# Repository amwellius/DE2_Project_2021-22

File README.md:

**2021**, Faculty of Electrical Engineering and Communication [FEKT](https://www.fekt.vut.cz/) <br/> 
 <br/>
# WATER TANK CONTROLLER

### Team members

- **Gregor Karetka**   &nbsp;                             *id=221053*   &nbsp;&nbsp;    <br/> 
- **Martin Knob**   &nbsp;&nbsp;&nbsp;&nbsp;&nbsp;               *id=221054*   &nbsp;&nbsp;     <br/>
- **Filip Kocum**   &nbsp;&nbsp;&nbsp;&nbsp;&nbsp;&nbsp;   *id=221055*   &nbsp;&nbsp;     <br/> 
- **Samuel Košík**   &nbsp;&nbsp;&nbsp;&nbsp;              *id=221056*   &nbsp;&nbsp;    <br/> 

Link to this file in GitHub repository:

[https://github.com/amwellius/DE2_Project_2021-22](https://github.com/amwellius/DE2_Project_2021-22)

### Table of contents

* [Project objectives](#objectives)
* [Hardware description](#hardware)
* [Libraries description](#libs)
* [Main application](#main)
* [Video and Documentation](#video)
* [References](#references)

## Project objectives

This simple but useful application will help you to fully control your **water tank** (not only!) in the garden. Do you want to know how much water is left? Do you want to refill the tank? Or are you interested in controlling your own independent application based on the volume left in the tank? <br/>
No problem! <br/>
With our **Water Tank Controller** you will be able to:
- know **current water level** in centimeters, percentage and liters,
- see **maximum** volume of the tank,
- use relays to control pump,
- prevent **owerflowing** the tank with extra sensor,
- see **graphic representation** of the water level.

## Hardware description

As main programming board **Arduino UNO** is used. For displaying results **Nokia 5110 LCD display** was selected, **Relay module** and **button** (optional). Ultrasonic **HC-SR04** is the primary water level sensor. There is **Capacitive Soil Moisture Sensor v1.2** used as backup to prevent overflowing the tank when debris (leaves, flowers, pollen, ...) clogs in the tank sink. By small adjustments in the code it can be transformed into rain detector. 

### Arduino UNO + breadboard 
[Datasheet](https://github.com/amwellius/DE2_Project_2021-22/blob/main/Datasheets%20%2B%20DOCs/ATMega_328P_datasheet.pdf)

&nbsp;

&nbsp;

Application uses a number of digital I/O pins, analog input pins and 3.3 V and 5 V power supply. Schematic can be seen here [SCHEMATIC](https://github.com/amwellius/DE2_Project_2021-22/blob/main/schematic.pdf). 

### Nokia 5110 LCD display 
[Datasheet](https://github.com/amwellius/DE2_Project_2021-22/blob/main/Datasheets%20%2B%20DOCs/Nokia5110_datasheet.pdf)

&nbsp;

&nbsp;

All output data is shown on Nokia LCD display. Third party library has been edited in order to use it with *Arduino UNO* and image display function was implemented. Display's resolution **84x48**  allows to display many useful data or **graphic representation** of water level as well. Drawn images were converted to **byte arrays** to simplify the usege in *Microchip Studio*. <br/>
Picture below shows possible states. <br/>

<br/>
Also some resistors had to be used to properly connect LCD to Arduino board.

### Relay Module 
[Datasheet](https://components101.com/switches/5v-single-channel-relay-module-pinout-features-applications-working-datasheet)

&nbsp;

&nbsp;

Usage of relay(s) is optional. **C code** has implemented section which toggles the relay module by pressing **button** connected to Arduio UNO. It can be connected to pump or solenoid to enable watering plants or other uses of the water. **A capacitor** inserted in cicruit (as RL low pass filter) helps to stabilize *overoscillations* generated by the button. By using hardware filter we were able to implement button handling with interrupt.

### UltraSonic sensor HC-SR04
[Datasheet](https://github.com/amwellius/DE2_Project_2021-22/blob/main/Datasheets%20%2B%20DOCs/HCSR04.pdf)

&nbsp;

&nbsp;

Main sensor for measuring the water level of the tank is **HC-SR04**. After entering its **dimensions** the sensor is calibrated. Providing it with short 10us pulse will result in receiving 8 cycles of 40KHz signal. This will be given by *ECHO pin*, so received value will be the time the wave travelled to the water and back to the sensor. Final distance can be obtained by this equation: 

&nbsp;

&nbsp;

Where **t** is the received value on *ECHO pin* and **0.034** cames from the speed of sound *(340 m/s = 0.034 m/us)*. Sound wave travels from sensor to water, but from water to the sensor as well. That is why the result has to be devided by two. *Arduino UNO's* **timers** are used to measure width of received square signal. After calculation, distance in milimeters is returned. Its value is sent to other functions, so supplementary data can be sent to display on *Nokia LCD*.

### Capacitive Water Lever Sensor

[Datasheet](https://github.com/amwellius/DE2_Project_2021-22/blob/main/Datasheets%20%2B%20DOCs/water_level_sensor.pdf)

It is situated **a few centimeters** above main ultrasonic sensor. If ultrasonic **fails**, this option will prevent **overflowing** the water tank. Display will print **System overflow** message. Relay module can the programmed for specific behavior after getting to *overflow* stage, too (optional). <br/>
Sensor is connected to *analog input* pin, *GND* and *Vcc=5 V*. Its usage describes table below. <br/>
   
   | **Value** | **Results in** |
   | :-: | :-: |
   | <=850 | System working properly. |
   | >850 | System malfunction! |

&nbsp;

## Libraries description

Code for this application was written in **C**, compilated using **AVR/GNU C compiler** and **MicroChip Studio**. Project consists of several libraries, list of all files can be found below:
   - `main.h`- main function header,
   - `main.c` - includes main procedures and functions,
   - `english_font.h` - characters for LCD display,
   - `nokia_5110_lcd.h` - header for LCD display,
   - `nokia_5110_lcd.c` - functions for LCD controlling,
   - `water_symbols.h` - header for c file,
   - `water_symbols.c` - byte maps (figures on LCD), 
   - `gpio.h` - input/output header,
   - `gpio.c` - input/output functions,
   - `timer.h` - header for timers in *Arduino UNO*,
   - `HC-SR04.h` - header for *ultrasonic sensor*,
   - `HC-SR04.c` - definitions for *ultrasonic sensor*.

All files are available here:
   [`main.h`](https://github.com/amwellius/DE2_Project_2021-22/blob/main/code/water_height_meter/main.h), [`main.c`](https://github.com/amwellius/DE2_Project_2021-22/blob/main/code/water_height_meter/main.c), [`english_font.h`](https://github.com/amwellius/DE2_Project_2021-22/blob/main/code/water_height_meter/english_font.h), [`nokia_5110_lcd.h`](https://github.com/amwellius/DE2_Project_2021-22/blob/main/code/water_height_meter/nokia_5110_lcd.h), [`nokia_5110_lcd.c`](https://github.com/amwellius/DE2_Project_2021-22/blob/main/code/water_height_meter/nokia_5110_lcd.c), [`water_symbols.h`](https://github.com/amwellius/DE2_Project_2021-22/blob/main/code/water_height_meter/water_symbols.h), [`water_symbols.c`](https://github.com/amwellius/DE2_Project_2021-22/blob/main/code/water_height_meter/water_symbols.c), [`gpio.h`](https://github.com/amwellius/DE2_Project_2021-22/blob/main/code/water_height_meter/gpio.h), [`gpio.c`](https://github.com/amwellius/DE2_Project_2021-22/blob/main/code/water_height_meter/gpio.c), [`timer.h`](https://github.com/amwellius/DE2_Project_2021-22/blob/main/code/water_height_meter/timer.h), [`HC-SR04.h`](https://github.com/amwellius/DE2_Project_2021-22/blob/main/code/water_height_meter/HC-SR04.h), [`HC-SR04.c`](https://github.com/amwellius/DE2_Project_2021-22/blob/main/code/water_height_meter/HC-SR04.c).

Some important parts of codes will be discuss. 

#### `main.c`
Example of controlling graphic representation of water level.
```c          
if (percentage == 100) selector = 10;
if (selector == 0) {            
    LCD_write_bytes_xy_defined_width((unsigned char*)water_level_default, 14, 70, bucket_x, bucket_y);
} else {
    LCD_write_bytes_xy_defined_width((unsigned char*)all_water_states[selector], 14, 70, bucket_x, bucket_y);
}            

// display maximum
itoa(tank_volume, distance_str, 10);
LCD_write_english_string(0, 0, "Vmax:");
LCD_write_english_string_continue(distance_str);
LCD_write_english_string_continue(" L");
```

#### `nokia_5110_lcd.h`
Functions used to control LCD Nokia Display.
```c
void LCD_clear();
void LCD_init();
void LCD_write_byte(unsigned char dat, unsigned char command);
void LCD_write_english_string(unsigned char X,unsigned char Y,char *s);
void LCD_write_english_string_continue(char *s);
void LCD_write_english_string_continue_precise(char *s, uint16_t data_len);
void LCD_write_char(unsigned char c);
void LCD_set_XY(unsigned char X, unsigned char Y);
void LCD_write_init();
void LCD_write_whole_screen(unsigned char *cells, uint16_t cells_n, uint16_t start_x, uint16_t start_y);
void LCD_write_bytes_xy_defined_width(unsigned char *cells, uint16_t width, uint16_t size, uint16_t x, uint16_t y);
```

#### `water_symbols.c`
Example of byte map (icon of 70% left).
```c
const unsigned char water_level_70[] = {
    // 'water level 70%', 14x35px
    0xfe, 0x01, 0x01, 0x01, 0x01, 0x01, 0x01, 0x01, 0x01, 0x01, 0x01, 0x01, 0x01, 0xfe, 0xff, 0x00,
    0xf8, 0xf8, 0xf8, 0xf8, 0xf8, 0xf8, 0xf8, 0xf8, 0xf8, 0xf8, 0x00, 0xff, 0xff, 0x00, 0xff, 0xff,
    0xff, 0xff, 0xff, 0xff, 0xff, 0xff, 0xff, 0xff, 0x00, 0xff, 0xff, 0x00, 0xff, 0xff, 0xff, 0xff,
    0xff, 0xff, 0xff, 0xff, 0xff, 0xff, 0x00, 0xff, 0x07, 0x04, 0x05, 0x05, 0x05, 0x05, 0x05, 0x05,
    0x05, 0x05, 0x05, 0x05, 0x04, 0x07
};
```

#### `HC-SR04.c`
Calculation of water level distance.
```c
TCCR1B |= (1 << ICES1);                                             // Reset to rising edge
        falling = ICR1;                                             // Read value ticks
        counts = falling - rising;                                  // Calc. difference between start and stop of the pulse
        dist = ((US_PER_COUNT * (uint32_t)counts) * 340) / 2000;    // Distance in mm
        
        for (int8_t i = 9; i >= 1; i--) {
            dist_vals[i] = dist_vals[i-1];
        }
        dist_vals[0] = dist;
```

## Main application

The main purpose of this application is to automatize operation of regulating water level in specified tank. After knowing **volume of owned tank**, ultrasonic sensor connected to *Arduino UNO* board will measure the water level. *LCD Nokia 5110* display shows water level in *centimeters*, *percentage* and *maximum usable volume of the water-tank*. Application uses **one extra sensor** to control the maximum volume. It is situated few centimeters **above** the max bound of water (we do not want to fill the tank completely to prevent owerflow). If the water reaches this sensor LCD shows problem **(`Owerflow`, `Error`)** depending on the value of ultrasonic sensor.

Our product has the ability to interact with relay modules for external usage. These can be used to replenish the tank, irrigation pump control, DC fans, windows opening, and others. 

### How to use
1. Mount *Ultrasonic sensor* on the top of water tank. Sensor's reference **zero (100%)** is set to be 4 centimeters from the ultrasonic transceiver.
2. Mount *Capacitive sensor* about **1 centimeter** above max water height. (If ultrasonic fails, capacitive sensor will save it from drowning).
3. Insert dimensions of your water tank into *C code*. If maximum height of your tank is e.g. 100 cm, than insert only 96 cm, to prevent owerflow.
   ```c
   // Tank Volume
   //**Enter values in cm !
   #define TANK_X  ((uint32_t)80)
   #define TANK_Y  ((uint32_t)80)
   #define TANK_Z  ((uint32_t)96)
   ```
4. Application is now set up. The *Nokia LCD screen* provides needed information according figure below. User can see data as
   - MAX volume of the tank in liters: `Vmax:800 L`,
   - Actual volume of water in the tank in liters: `Vact:441 L`,
   - Actual volume of water in the tank in percentage: `Vact:55 %`,
   - Actual volume of water represented by a up-time graphic icon,
   - System status message: `OK`, `ERROR`, `OVERFLOW`.
   <br/>

6. Relay module is set to interact with pressing installed button. **Do not** hesitate to use your creativity and relay module (modules) on your own by simply editing the code. 

### Possible Stages
After powering on, test screen procedure runs (represented by `DE2 Water System` screen and `graphic tank icon` filling up). System is ready to operate! 

#### System OK
Level of water in tank is between **0** and **100%**, *capacitive sensor* is not activated by water reaching its level; system working correctly.

#### System ERROR
Rises when unexpected data is measured. 
   - Bad *ultrasonic calibration*, too close *(<4 cm)* or too far *(>400 cm)*,
   - Bad tank dimensions,
   - Capacitor used with relay module and button not connected properly,
   - Apocalypse.  

#### System OVERFLOW
*Ultrasonic sensor* occurred **problem**. Water reaches *capacitive sensor*. Different data received from two sensors leads to system `Overflow` stage message.

## Video and Documentation

**Video available here:** <br/>
   [Link to YouTube](https://www.youtube.com/watch?v=HSv_cm3vf8U) 

**HEX file available here:** <br/>
   [HEX file](https://github.com/amwellius/DE2_Project_2021-22/blob/main/code/water_height_meter/HEX%20files/water_height_meter.hex)
   
**Documentation available here:** <br/>
As PDF [file](https://github.com/amwellius/DE2_Project_2021-22/blob/main/code/water_height_meter/docs/latex/refman.pdf)
or as [doxygen generated website](https://github.com/amwellius/DE2_Project_2021-22/tree/main/code/water_height_meter/docs/html) (download required, open index.html)

### Schematic

### FSM 

## References

### Used materials:
   - Theoretical knowledge from Digital-Electronics-2, 2021 > [Link](https://moodle.vut.cz/course/view.php?id=242365)
   - Lab classes **DE2** > [Link](https://github.com/tomas-fryza/Digital-electronics-2)
   - Byte Arrays Generator > [Link](https://javl.github.io/image2cpp/)
   - LaTeX equation editor > [Link](https://www.codecogs.com/latex/eqneditor.php)

   ### Used programs and its links:
   - [MicroChip Studio](https://www.microchip.com/en-us/development-tools-tools-and-software/microchip-studio-for-avr-and-sam-devices)
   - [SimulIDE](https://www.simulide.com/p/home.html)
   - [GitHub](https://github.com/)
   - [GitHub Desktop](https://desktop.github.com/)
   - [Git Bash](https://git-scm.com/download/win)
   - [KiCAD](https://componentsearchengine.com/library/kicad?gclid=CjwKCAiAksyNBhAPEiwAlDBeLB2QSESyWl1669aV7oK23ZJxxCjH-YFDBnxbHhdrZ5DbmMH_Wg5LuBoCEQUQAvD_BwE)

All pictures have been taken in DE2 Laboratories!
   
________________________________________________________________________________
©2021, VUT FEKT, Brno, Czech Republic <br/>
Košík, Karetka, Kocum, Knob <br/>
**For Educational Purposes Only!**

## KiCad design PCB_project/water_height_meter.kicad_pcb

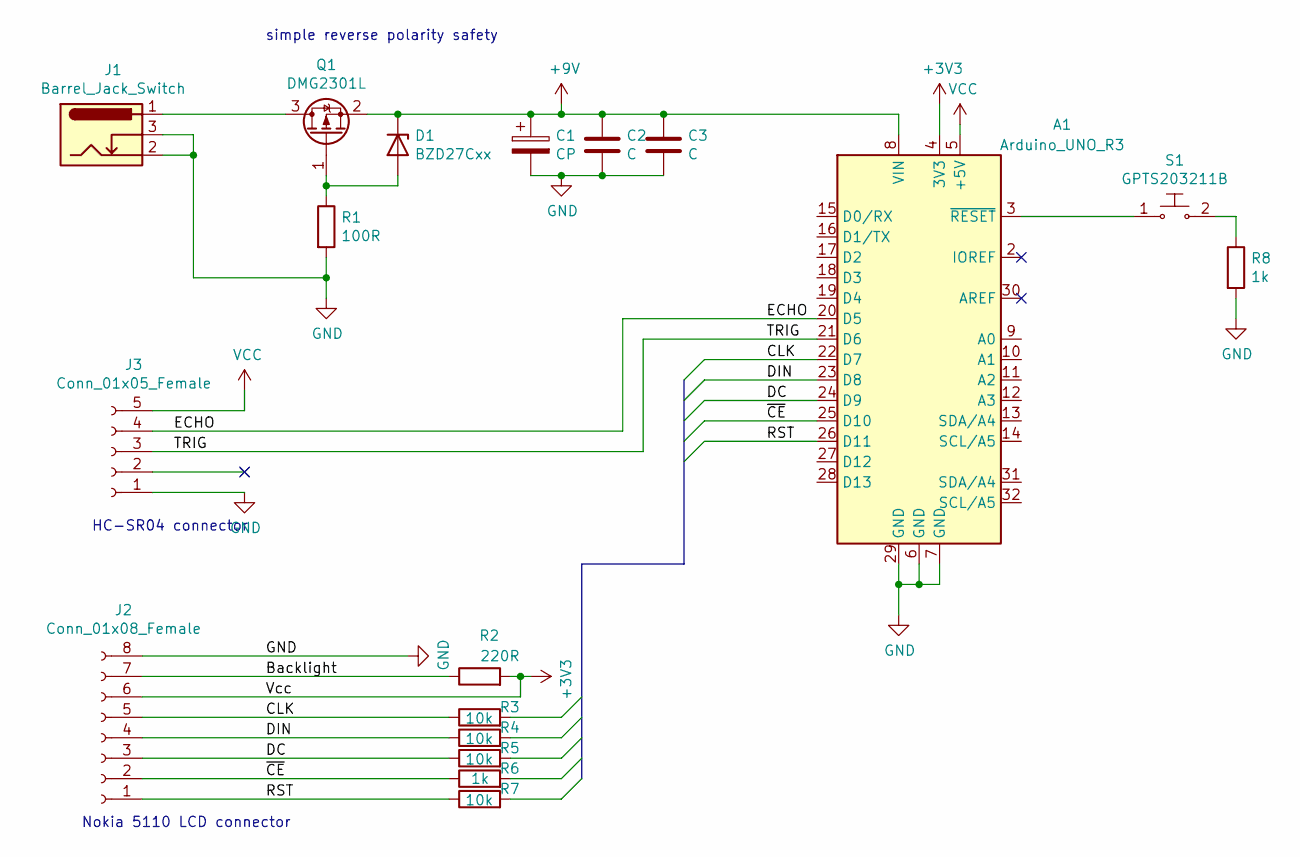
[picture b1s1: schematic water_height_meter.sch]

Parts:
A1: Arduino_UNO_R3
C1: CP; CP_Radial_D6.3mm_P2.50mm
C2, C3: C; C_0805_2012Metric_Pad1.18x1.45mm_HandSolder
D1: BZD27Cxx; D_SMF
J1: Barrel_Jack_Switch; BarrelJack_Wuerth_6941xx301002
J2: Conn_01x08_Female; PinHeader_1x08_P2.54mm_Vertical
J3: Conn_01x05_Female; PinHeader_1x05_P2.54mm_Vertical
Q1: DMG2301L; SOT-23
R1: 100R; R_1206_3216Metric_Pad1.42x1.75mm_HandSolder
R2: 220R; R_0603_1608Metric_Pad1.05x0.95mm_HandSolder
R3, R4, R5, R7: 10k; R_0603_1608Metric_Pad1.05x0.95mm_HandSolder
R6, R8: 1k; R_0603_1608Metric_Pad1.05x0.95mm_HandSolder
S1: GPTS203211B; PushButton_12x12mm_THT_GPTS203211B; MPN GPTS203211B; Digi-Key_PN CW181-ND

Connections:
+3V3: A1.4 (3V3), J2.6, R2.2
+9V: A1.8 (VIN), C1.1, C2.1, C3.1, D1.1 (K), Q1.2 (S)
/Backlight: J2.7, R2.1
/CLK: A1.22 (D7), J2.5, R3.1
/DC: A1.24 (D9), J2.3, R5.1
/DIN: A1.23 (D8), J2.4, R4.1
/ECHO: A1.20 (D5), J3.4
/RST: A1.26 (D11), J2.1, R7.1
/TRIG: A1.21 (D6), J3.3
/~CE: A1.25 (D10), J2.2, R6.1
GND: A1.6 (GND), A1.7 (GND), A1.29 (GND), C1.2, C2.2, C3.2, J1.2, J1.3, J2.8, J3.1, R1.2, R8.2
unnamed: A1.3 (~RESET), S1.1
unnamed: D1.2 (A), Q1.1 (G), R1.1
unnamed: J1.1, Q1.3 (D)
unnamed: R8.1, S1.2
VCC: A1.5 (+5V), J3.5

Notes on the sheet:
simple reverse polarity safety
HC-SR04 connector
Nokia 5110 LCD connector

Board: 2 copper layers, 18 parts (0 on the bottom side), 16 nets, no tracks yet.

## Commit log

2021-11-20 Add basic schemtic and lcd code
2021-11-20 Add logo display and possibility to display it
2021-11-20 Update schematic
2021-11-22 added HCSR04 datasheet
2021-11-22 added images and docs
2021-11-24 Add Arduino UNO pinout
2021-11-24 Add string example
2021-11-24 add schematic
2021-11-24 added components
2021-11-24 Add multiple include possibility
2021-11-24 [project]project
2021-11-24 Add gitignore
2021-11-24 Remove gitignore files
2021-11-24 Gitignore pcb - remove files
2021-11-25 Add ultrasound meter
2021-11-28 added water level icons and code
2021-11-29 Add moisture sensor
2021-11-29 Add nokia picture displaying function
2021-11-29 Update nokia display driver
2021-11-30 Fix many things
2021-11-30 added navrh
2021-12-02 Add moisture sensor, relay and button
    + moisture
    + capacitive
    + relay
2021-12-06 add pictures
2021-12-06 ass water states img
2021-12-07 add correted images
2021-12-08 add comments
2021-12-10 Add schematic to readme
2021-12-10 Add Doxygen
2021-12-10 Update docs
2021-12-10 Add HC docs
2021-12-10 add documentation for files
2021-12-10 Add latex
2021-12-15 Update README.md
    spelling corrections and last edits
2021-12-16 Add FSM
2021-12-16 Update hex file
